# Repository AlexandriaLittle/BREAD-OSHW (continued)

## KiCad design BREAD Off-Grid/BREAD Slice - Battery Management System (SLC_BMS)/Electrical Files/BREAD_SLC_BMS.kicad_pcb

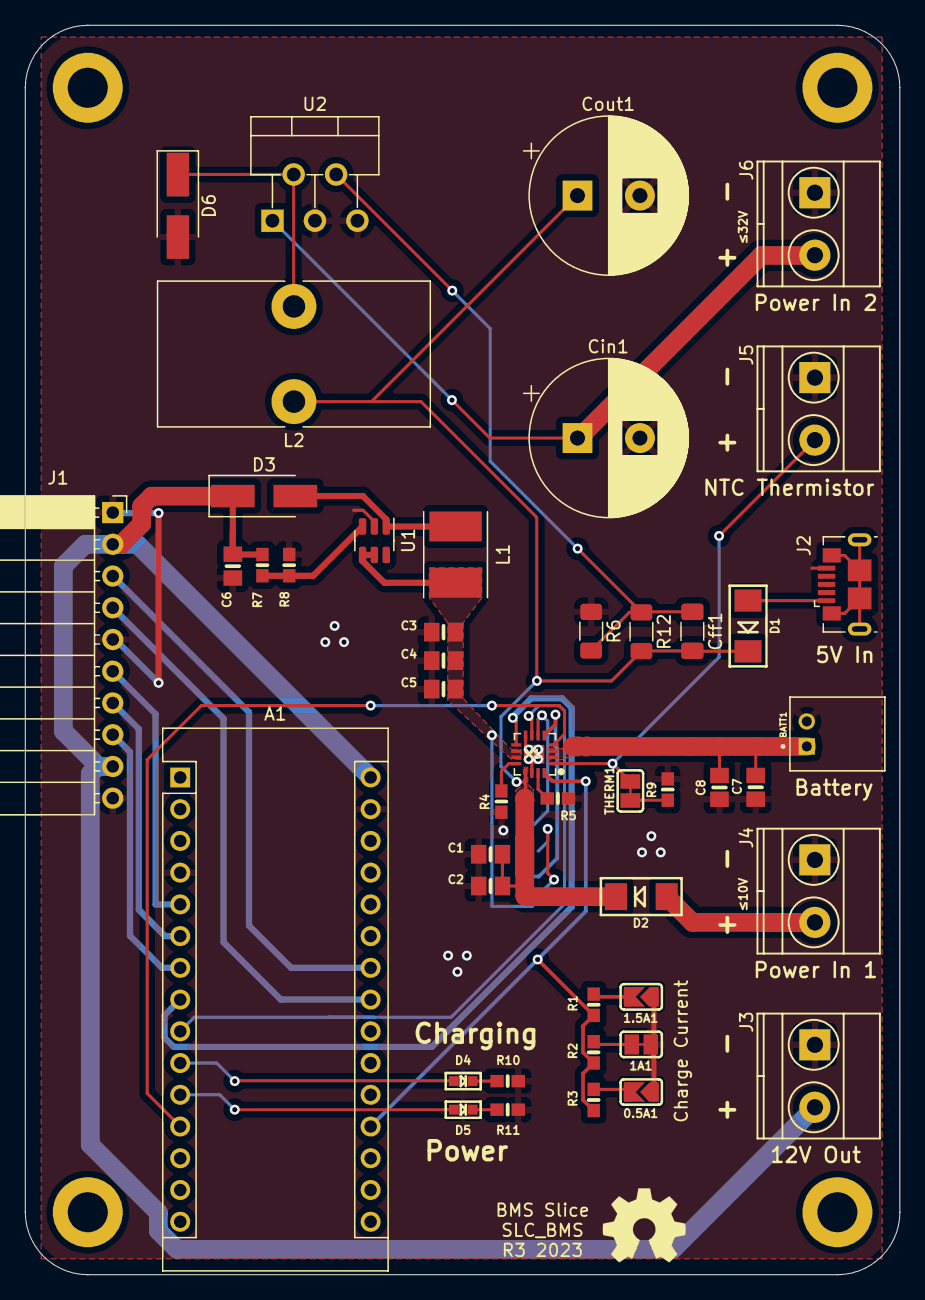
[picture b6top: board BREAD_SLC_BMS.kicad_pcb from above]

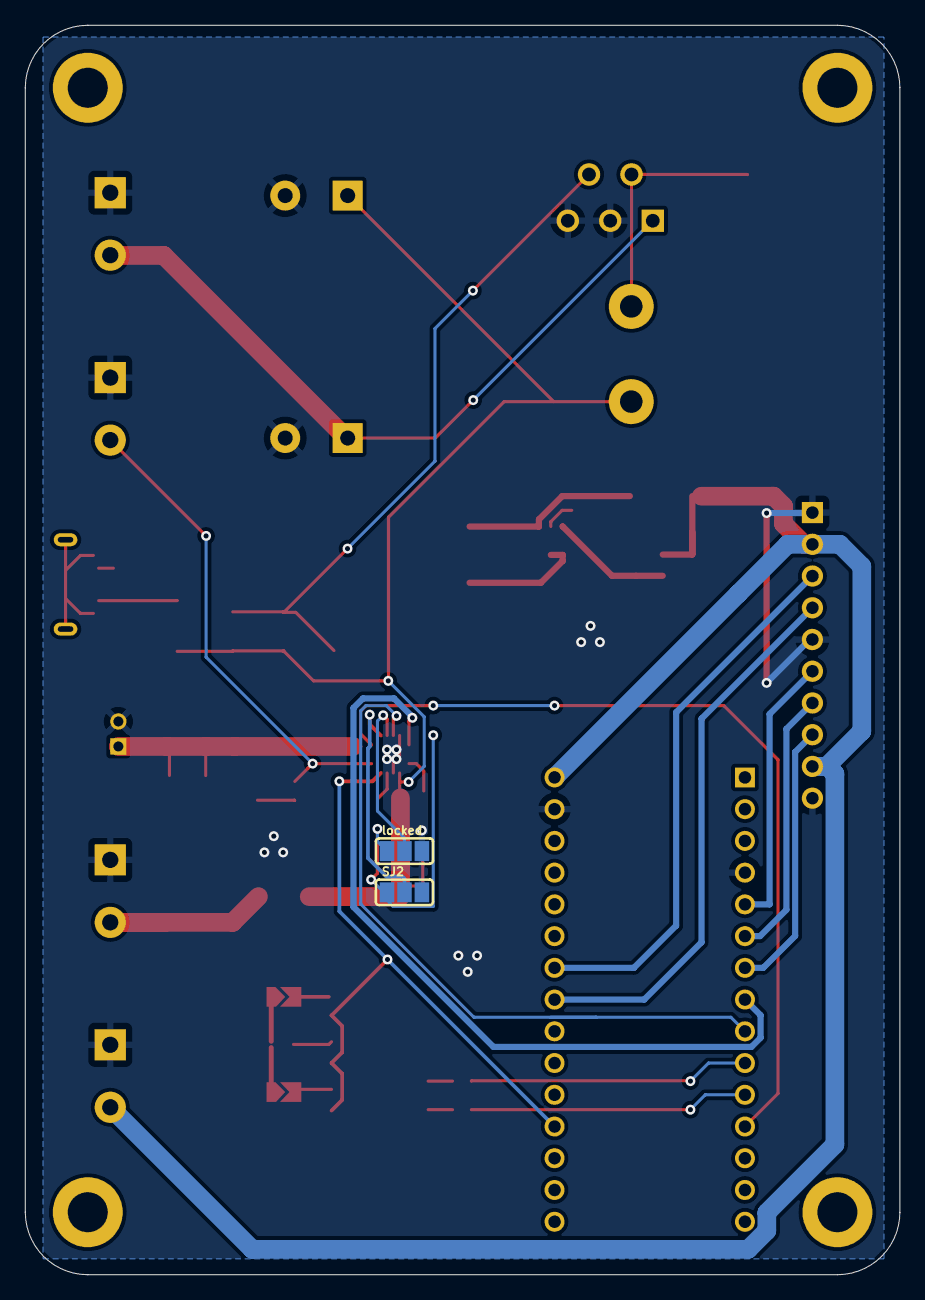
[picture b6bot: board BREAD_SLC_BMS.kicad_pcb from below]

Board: 2 copper layers, 70.0 x 100.0 mm, 53 parts (2 on the bottom side), 34 nets.

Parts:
0.5A1, 1.5A1: SOLDERJUMPER; SOLDERJUMPER_ARROW_NOPASTE
1A1: SOLDERJUMPERCLOSED; SOLDERJUMPER_CLOSEDWIRE
A1: Arduino_Nano_v3.x; Arduino_Nano
BATT1: JST 2PH; JST_S2B-PH-K-S(LF)(SN)
C1, C2, C7, C8: 10uF; 0805-NO
C3, C6: 22uF; 0805-NO
C4, C5: C; 0805-NO
Cff1: 3.3nF; C_1206_3216Metric_Pad1.33x1.80mm_HandSolder
Cin1: 680uF; CP_Radial_D12.5mm_P5.00mm
Cout1: 470uF; CP_Radial_D12.5mm_P5.00mm
D1, D2: SK34A; SMADIODE
D3, D6: D_Schottky; D_SMA_Handsoldering
D4: RED; CHIPLED_0603
D5: GREEN; CHIPLED_0603
H1, H2, H3, H4: MountingHole; MountingHole_3.2mm_M3_DIN965_Pad
J1: Conn_01x10_Female; PinSocket_1x10_P2.54mm_Horizontal
J2: USB_B_Micro; USB_Micro-B_GCT_USB3076-30-A
J3, J4, J5, J6: Screw_Terminal_01x02; TerminalBlock_Pheonix_MKDS1.5-2pol
L1: 22uH; L_Taiyo-Yuden_NR-50xx_HandSoldering
L2: 53uH; L_Toroid_Vertical_L21.6mm_W11.4mm_P7.62mm_Pulse_KM-3
Logo1: Logo_Open_Hardware_Small; OSHW-Symbol_6.7x6mm_SilkScreen
R1: 590; 0603-NO
R2, R4: 1K; 0603-NO
R3: 2K; 0603-NO
R5, R9, R10, R11: 10K; 0603-NO
R6: 1k; R_1206_3216Metric_Pad1.30x1.75mm_HandSolder
R7: 39k; 0603-NO
R8: 2.2k; 0603-NO
R12: 4.7k; R_1206_3216Metric_Pad1.30x1.75mm_HandSolder
SJ2: SOLDERJUMPER_2WAY; SOLDERJUMPER_2WAY_OPEN_NOPASTE
THERM1: SOLDERJUMPERCLOSED; SOLDERJUMPER_CLOSEDWIRE
U1: MT3608; SOT-23-6
U2: LM2596S-ADJ; TO-220-5_P3.4x3.7mm_StaggerOdd_Lead3.8mm_Vertical
X1: BQ24074; QFN16_3MM
locked: SOLDERJUMPER_2WAY; SOLDERJUMPER_2WAY_OPEN_NOPASTE

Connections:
/CHGI: A1.10 (D7), D4.A
/CHG_EN: A1.12 (D9), X1.4 (~CE)
/EN1: X1.6 (EN1), locked.2
/EN2: SJ2.2, X1.5 (EN2)
/E_STOP: A1.5 (D2), J1.6
/I2C_CLK: A1.24 (A5), J1.3
/I2C_DAT: A1.23 (A4), J1.4
/ILIM: R4.1, X1.12 (ILIM)
/INT: A1.6 (D3), J1.7
/ISET: A1.19 (A0), R1.1, R2.1, R3.1, X1.16 (ISET)
/ITERM: R5.1, X1.15 (ITERM)
/OUT: C3.1, C4.1, C5.1, L1.1, SJ2.1, U1.4 (EN), U1.5 (IN), X1.10 (OUT), X1.11 (OUT), locked.1
/PGOODI: A1.11 (D8), D5.A
/PWR: A1.30 (VIN), C6.1, D3.1 (K), J1.2, J1.9, J3.2, R7.1
/SYNC: A1.7 (D4), J1.8
/THERM: J5.2, THERM1.2, X1.1 (TS)
/Vmotor: Cin1.1, J6.2, U2.1 (VIN)
/~CHG: A1.8 (D5), X1.9 (~CHG)
/~PGOOD: A1.9 (D6), X1.7 (~PGOOD)
GND: 0.5A1.1, 1.5A1.1, 1A1.1, A1.4 (GND), A1.29 (GND), BATT1.2 (1), C1.2, C2.2, C3.2, C4.2, C5.2, C6.2, C7.2, C8.2, Cin1.2, Cout1.2, D6.2 (A), J1.1, J1.5, J1.10, J2.5 (GND), J3.1, J4.1, J5.1, J6.1, R4.2, R5.2, R6.1, R8.2, R9.2, R10.2, R11.2, SJ2.3, U1.2 (GND), U2.3 (GND), U2.5 (~ON/OFF), X1.8 (VSS), X1.14 (TMR), X1.THERMAL (VSS), locked.3
unnamed: 0.5A1.2, R3.2
unnamed: 1.5A1.2, R1.2
unnamed: 1A1.2, R2.2
unnamed: Cff1.1, R6.2, R12.1, U2.4 (FB)
unnamed: D1.A, J2.1 (VBUS)
unnamed: D2.A, J4.2
unnamed: D3.2 (A), L1.2, U1.1 (SW)
unnamed: D4.C, R10.1
unnamed: D5.C, R11.1
unnamed: D6.1 (K), L2.1, U2.2 (OUT)
unnamed: R7.2, R8.1, U1.3 (FB)
unnamed: R9.1, THERM1.1
VBUS: C1.1, C2.1, Cff1.2, Cout1.1, D1.C, D2.C, L2.2, R12.2, X1.13 (IN)
VLIPO: BATT1.1 (2), C7.1, C8.1, X1.2 (BAT), X1.3 (BAT)

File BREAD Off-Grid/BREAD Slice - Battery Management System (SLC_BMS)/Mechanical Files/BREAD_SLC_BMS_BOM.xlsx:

KiCad Reference | Part Number | Description | Value | Quantity | Unit Cost | Total Cost | Link
A1 | A000005 | Arduino Nano |  | 1 | 23.67 | 23.67 | https://store.arduino.cc/products/arduino-nano
 | PEC15SACN | Male headers | 0.1” pitch, 15-pin | 2 | 1.41 | 2.82 | https://www.digikey.com/en/products/detail/sullins-connector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
 | PPTC151LFBN-RC | Female headers | 0.1” pitch, 15-pin | 2 | 0.98 | 1.96 | https://www.digikey.com/en/products/detail/sullins-connector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
BATT1 | S2B-PH-K-S(LF)(SN) | Battery connector | 2 mm pitch, 2-position, right angle | 1 | 0.17 | 0.17 | https://www.digikey.com/en/products/detail/jst-sales-america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
C1, C2, C7, C8 | CL21A106KOQNNNE | Non-polarized capacitors | 10 μF, 0805 | 4 | 0.1 | 0.4 | https://www.digikey.com/en/products/detail/samsung-electro-m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
C3, C6 | CL21A226MOQNNNE | Non-polarized capacitors | 22 μF, 0805 | 2 | 0.27 | 0.54 | https://www.digikey.com/en/products/detail/samsung-electro-m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
Cff1 | C1206C332J5GAC7800 | Non-polarized capacitor | 3.3 nF, 1206 | 1 | 0.3 | 0.3 | https://www.digikey.com/en/products/detail/kemet/C1206C332J5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
Cin1 | EEU-FC1J681L | Polarized capacitor | 680 μF | 1 | 1.94 | 1.94 | https://www.digikey.com/en/products/detail/panasonic-electro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
Cout1 | EEU-FR1H471B | Polarized capacitor | 470 μF | 1 | 1.31 | 1.31 | https://www.digikey.com/en/products/detail/panasonic-electro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
D1, D2 | SK34A | Schottky diodes | SK34A | 2 | 0.49 | 0.98 | https://www.digikey.com/en/products/detail/smc-diode-solutio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
D3 | SS34-HF | Schottky diode | SS34 | 1 | 0.45 | 0.45 | https://www.digikey.com/en/products/detail/comchip-technolog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
D4 | B1911USD-20D000114U1930 | LED | Red, 0603 | 1 | 0.1 | 0.1 | https://www.digikey.com/en/products/detail/harvatek-corporat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
D5 | B1911NG--20D000214U1930 | LED | Green, 0603 | 1 | 0.1 | 0.1 | https://www.digikey.com/en/products/detail/harvatek-corporat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
D6 | CDBA540-HF | Schottky diode | CDBA540-HF | 1 | 0.44 | 0.44 | https://www.digikey.com/en/products/detail/comchip-technolog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
J1 | PPTC101LGBN-RC | Female header | 0.1” pitch, 10-pin, right angle | 1 | 0.76 | 0.76 | https://www.digikey.com/en/products/detail/sullins-connector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
J2 | USB3076-30-A | Micro USB connector | USB3076 | 1 | 0.7 | 0.7 | https://www.digikey.com/en/products/detail/gct/USB3076-30-A/9859635
J3 - J6 | 1935776 | Terminal blocks | 5mm pitch, 2-position, right angle | 4 | 0.59 | 2.36 | https://www.digikey.com/en/products/detail/phoenix-contact/1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
L1 | NRS5020T220MMGJ | Inductor | 22 μH | 1 | 0.3 | 0.3 | https://www.digikey.com/en/products/detail/taiyo-yuden/NRS50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
L2 | PE-54039NL | Inductor | 53 μH | 1 | 4.42 | 4.42 | https://www.digikey.com/en/products/detail/pulse-electronics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
R1 | RMCF0603FT590R | Resistor | 590Ω, 0603 | 1 | 0.1 | 0.1 | https://www.digikey.com/en/products/detail/stackpole-electro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
R2, R4 | RNCP0603FTD1K00 | Resistors | 1k Ω, 0603 | 2 | 0.1 | 0.2 | https://www.digikey.com/en/products/detail/stackpole-electro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
R3 | RMCF0603FT2K00 | Resistor | 2k Ω, 0603 | 1 | 0.1 | 0.1 | https://www.digikey.com/en/products/detail/stackpole-electro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
R5, R9 - R11 | RNCP0603FTD10K0 | Resistors | 10k Ω, 0603 | 4 | 0.1 | 0.4 | https://www.digikey.com/en/products/detail/stackpole-electro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
R6 | RMCF1206FT1K00 | Resistor | 1k Ω, 1206 | 1 | 0.1 | 0.1 | https://www.digikey.com/en/products/detail/stackpole-electro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
R7 | RMCF0603FT39K0 | Resistor | 39k Ω, 0603 | 1 | 0.1 | 0.1 | https://www.digikey.com/en/products/detail/stackpole-electro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
R8 | RMCF0603FT2K20 | Resistor | 2.2k Ω, 0603 | 1 | 0.1 | 0.1 | https://www.digikey.com/en/products/detail/stackpole-electro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
R12 | RMCF1206FT4K70 | Resistor | 4.7k Ω, 1206 | 1 | 0.1 | 0.1 | https://www.digikey.com/en/products/detail/stackpole-electro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
U1 | MT3608 | Boost converter | MT3608 | 1 | 0.09 | 0.43 | https://www.lcsc.com/product-detail/DC-DC-Converters_XI-AN-A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
U2 | LM2596TVADJG | Voltage regulator | LM2596 | 1 | 2.79 | 2.79 | https://www.digikey.com/en/products/detail/onsemi/LM2596TVAD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
X1 | BQ24074RGTR | Charging chip | BQ24074 | 1 | 3.45 | 3.45 | https://www.digikey.com/en/products/detail/texas-instruments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

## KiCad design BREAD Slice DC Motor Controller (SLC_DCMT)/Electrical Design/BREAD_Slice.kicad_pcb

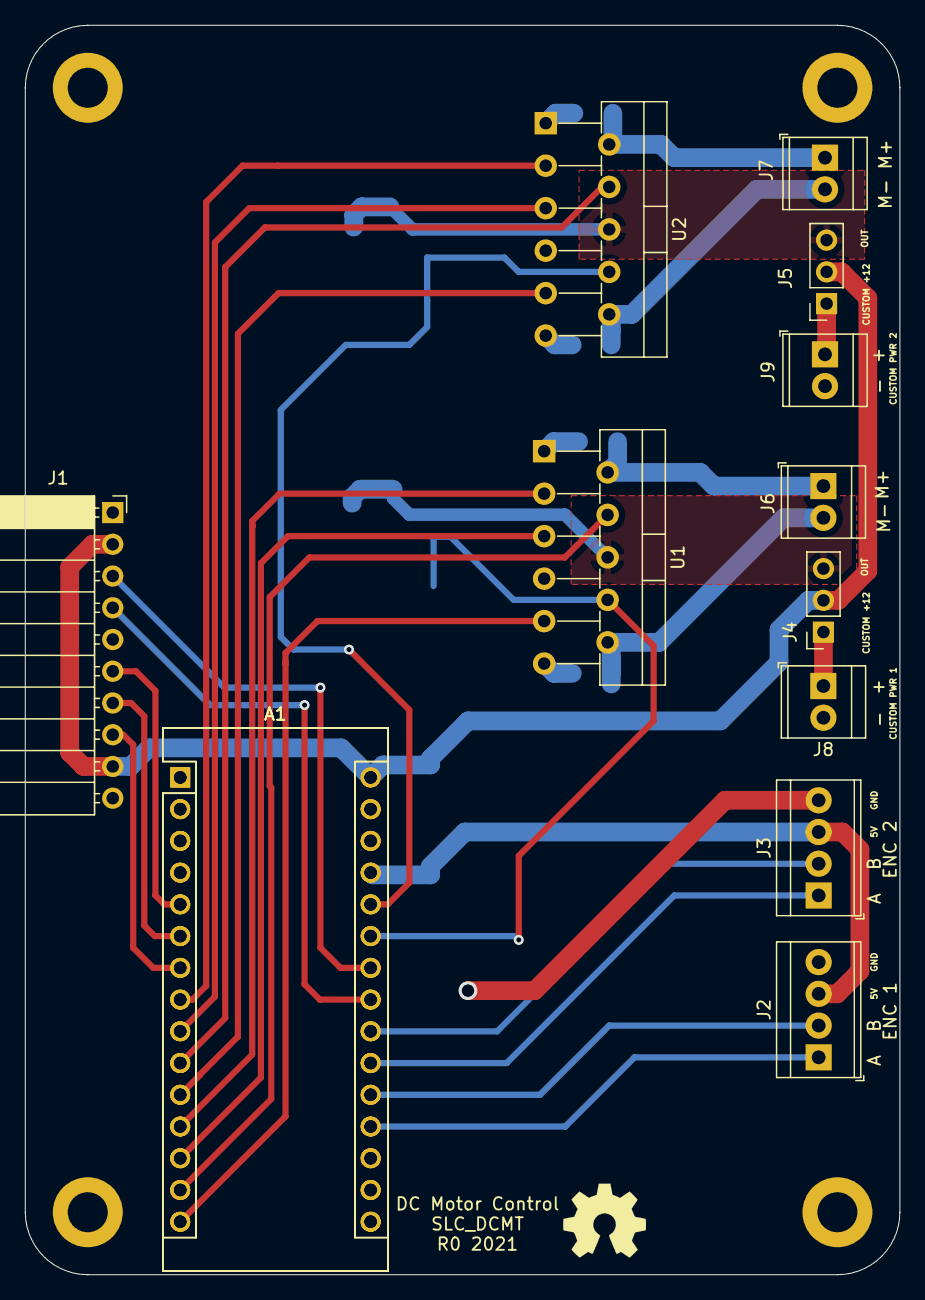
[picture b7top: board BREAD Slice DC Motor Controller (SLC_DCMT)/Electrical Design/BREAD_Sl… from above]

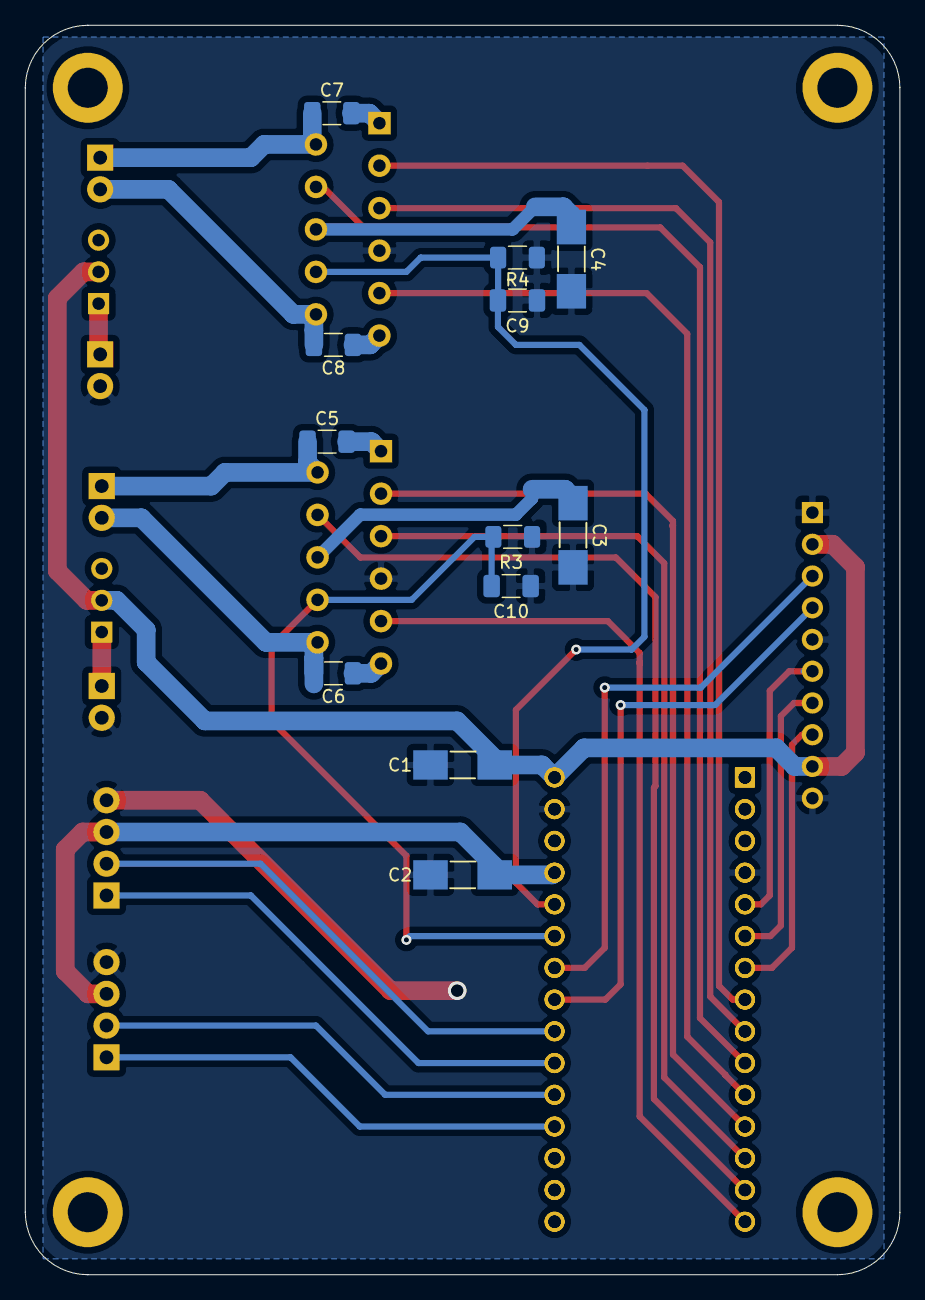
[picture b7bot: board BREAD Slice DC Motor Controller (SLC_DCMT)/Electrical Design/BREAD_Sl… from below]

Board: 2 copper layers, 70.0 x 100.0 mm, 30 parts (12 on the bottom side), 41 nets.

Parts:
A1, A1#2: Arduino_Nano_v3.x; Arduino_Nano
C1, C2, C3, C4: 10uF_t; C_2312
C5, C6, C7, C8, C9, C10: 10 nF; C_1206_3216Metric_Pad1.33x1.80mm_HandSolder
H1, H2, H3, H4: MountingHole; MountingHole_3.2mm_M3_DIN965_Pad
J1: Conn_01x10_Female; PinSocket_1x10_P2.54mm_Horizontal
J2, J3: Screw_Terminal_01x04; TerminalBlock_TE_282834-4_1x04_P2.54mm_Horizontal
J4, J5: Conn_01x03_Male; PinSocket_1x03_P2.54mm_Vertical
J6, J7, J8, J9: Screw_Terminal_01x02; TerminalBlock_TE_282834-2_1x02_P2.54mm_Horizontal
Logo1: Logo_Open_Hardware_Small; OSHW-Symbol_6.7x6mm_SilkScreen
R3, R4: 2.2 k; R_1206_3216Metric_Pad1.30x1.75mm_HandSolder
U1, U2: LMD18200; TO-220-11_P3.4x5.08mm_StaggerOdd_Lead4.85mm_Vertical

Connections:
+5V: A1.27, A1#2.27, C2.1, J2.3, J3.3
+12V: A1.30, A1#2.30, C1.1, J1.2, J1.9, J4.2, J5.2
/A1: A1.19, A1#2.19, J2.1
/A2: A1.21, A1#2.21, J3.1
/B1: A1.20, A1#2.20, J2.2
/B2: A1.22, A1#2.22, J3.2
/BR1: A1.14, A1#2.14, U1.4
/BR2: A1.10, A1#2.10, U2.4
/CSEN1: A1.25, A1#2.25, C10.1, R3.1, U1.8
/CSEN2: A1.26, A1#2.26, C9.1, R4.1, U2.8
/CUST1: J4.1, J8.1
/CUST2: J5.1, J9.1
/DIR1: A1.12, A1#2.12, U1.3
/DIR2: A1.8, A1#2.8, U2.3
/E_STOP: A1.5, A1#2.5, J1.6
/I2C_CLK: A1.24, A1#2.24, J1.3
/I2C_DAT: A1.23, A1#2.23, J1.4
/INT: A1.6, A1#2.6, J1.7
/MC1: A1.13, A1#2.13, U1.5
/MC2: A1.9, A1#2.9, U2.5
/SYNC: A1.7, A1#2.7, J1.8
/THRM1: A1.15, A1#2.15, U1.9
/THRM2: A1.11, A1#2.11, U2.9
GND: A1.4, A1.29, A1#2.4, A1#2.29, C1.2, C2.2, C3.2, C4.2, C9.2, C10.2, J1.1, J1.5, J1.10, J2.4, J3.4, J8.2, J9.2, R3.2, R4.2, U1.7, U2.7
unnamed: A1.1, A1#2.1
unnamed: A1.2, A1#2.2
unnamed: A1.3, A1#2.3
unnamed: A1.16, A1#2.16
unnamed: A1.17, A1#2.17
unnamed: A1.18, A1#2.18
unnamed: A1.28, A1#2.28
unnamed: C3.1, J4.3, U1.6
unnamed: C4.1, J5.3, U2.6
unnamed: C5.1, J6.1, U1.2
unnamed: C5.2, U1.1
unnamed: C6.1, U1.11
unnamed: C6.2, J6.2, U1.10
unnamed: C7.1, J7.1, U2.2
unnamed: C7.2, U2.1
unnamed: C8.1, U2.11
unnamed: C8.2, J7.2, U2.10

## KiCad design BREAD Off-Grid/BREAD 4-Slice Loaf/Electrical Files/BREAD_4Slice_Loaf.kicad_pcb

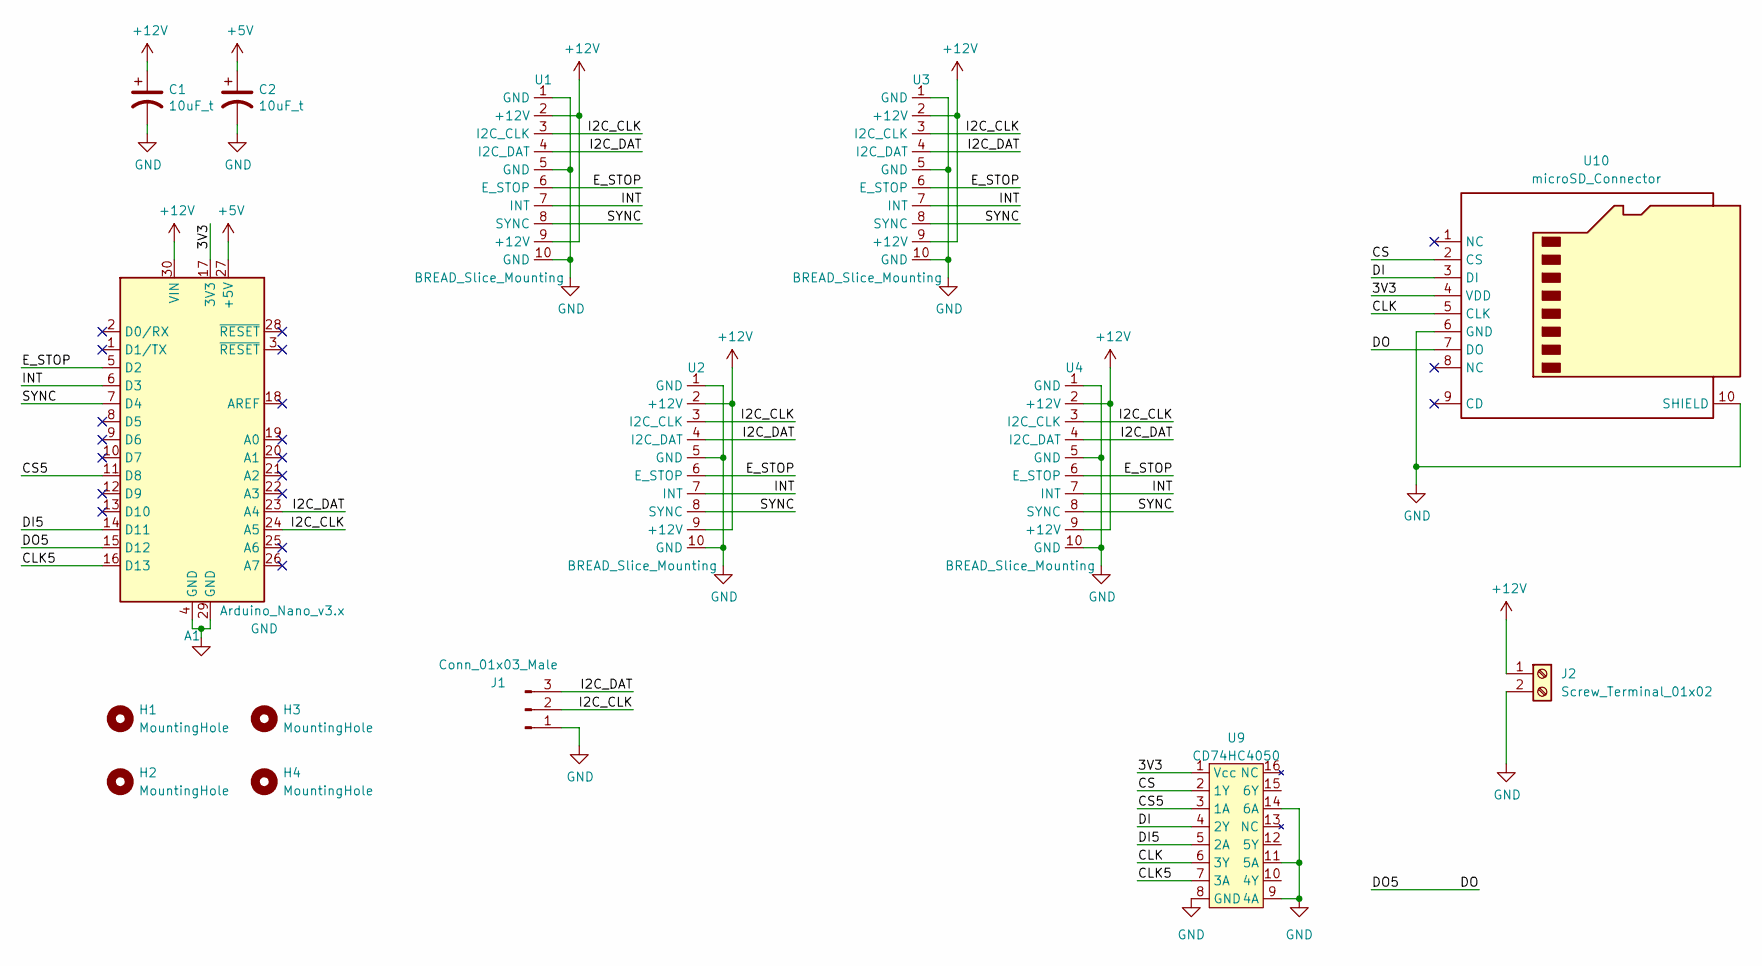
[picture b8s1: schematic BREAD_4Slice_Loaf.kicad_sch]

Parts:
A1: Arduino_Nano_v3.x; Arduino_Nano
C1, C2: 10uF_t; C_1206_3216Metric_Pad1.33x1.80mm_HandSolder; Part # T491C106K025AT
H1, H2, H3, H4: MountingHole; MountingHole_3.2mm_M3_DIN965_Pad
J1: Conn_01x03_Male; PinHeader_1x03_P2.54mm_Vertical
J2: Screw_Terminal_01x02; TerminalBlock_Phoenix_MKDS-1,5-2_1x02_P5.00mm_Horizontal
U1, U2, U3, U4: BREAD_Slice_Mounting
U9: CD74HC4050; DIP-16_W7.62mm_Socket_LongPads
U10: microSD_Connector; micro_SD_LOAF

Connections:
+5V: A1.27 (+5V), C2.1
+12V: A1.30 (VIN), C1.1, J2.1, U1.2 (+12V), U1.9 (+12V), U2.2 (+12V), U2.9 (+12V), U3.2 (+12V), U3.9 (+12V), U4.2 (+12V), U4.9 (+12V)
/3V3: A1.17 (3V3), U9.1 (Vcc), U10.4 (VDD)
/CLK: U9.6 (3Y), U10.5 (CLK)
/CLK5: A1.16 (D13), U9.7 (3A)
/CS: U9.2 (1Y), U10.2 (CS)
/CS5: A1.11 (D8), U9.3 (1A)
/DI: U9.4 (2Y), U10.3 (DI)
/DI5: A1.14 (D11), U9.5 (2A)
/DO: A1.15 (D12), U10.7 (DO)
/E_STOP: A1.5 (D2), U1.6 (E_STOP), U2.6 (E_STOP), U3.6 (E_STOP), U4.6 (E_STOP)
/I2C_CLK: A1.24 (A5), J1.2, U1.3 (I2C_CLK), U2.3 (I2C_CLK), U3.3 (I2C_CLK), U4.3 (I2C_CLK)
/I2C_DAT: A1.23 (A4), J1.3, U1.4 (I2C_DAT), U2.4 (I2C_DAT), U3.4 (I2C_DAT), U4.4 (I2C_DAT)
/INT: A1.6 (D3), U1.7 (INT), U2.7 (INT), U3.7 (INT), U4.7 (INT)
/SYNC: A1.7 (D4), U1.8 (SYNC), U2.8 (SYNC), U3.8 (SYNC), U4.8 (SYNC)
GND: A1.4 (GND), A1.29 (GND), C1.2, C2.2, J1.1, J2.2, U1.1 (GND), U1.5 (GND), U1.10 (GND), U2.1 (GND), U2.5 (GND), U2.10 (GND), U3.1 (GND), U3.5 (GND), U3.10 (GND), U4.1 (GND), U4.5 (GND), U4.10 (GND), U9.8 (GND), U9.9 (4A), U9.11 (5A), U9.14 (6A), U10.6 (GND), U10.10 (SHIELD)

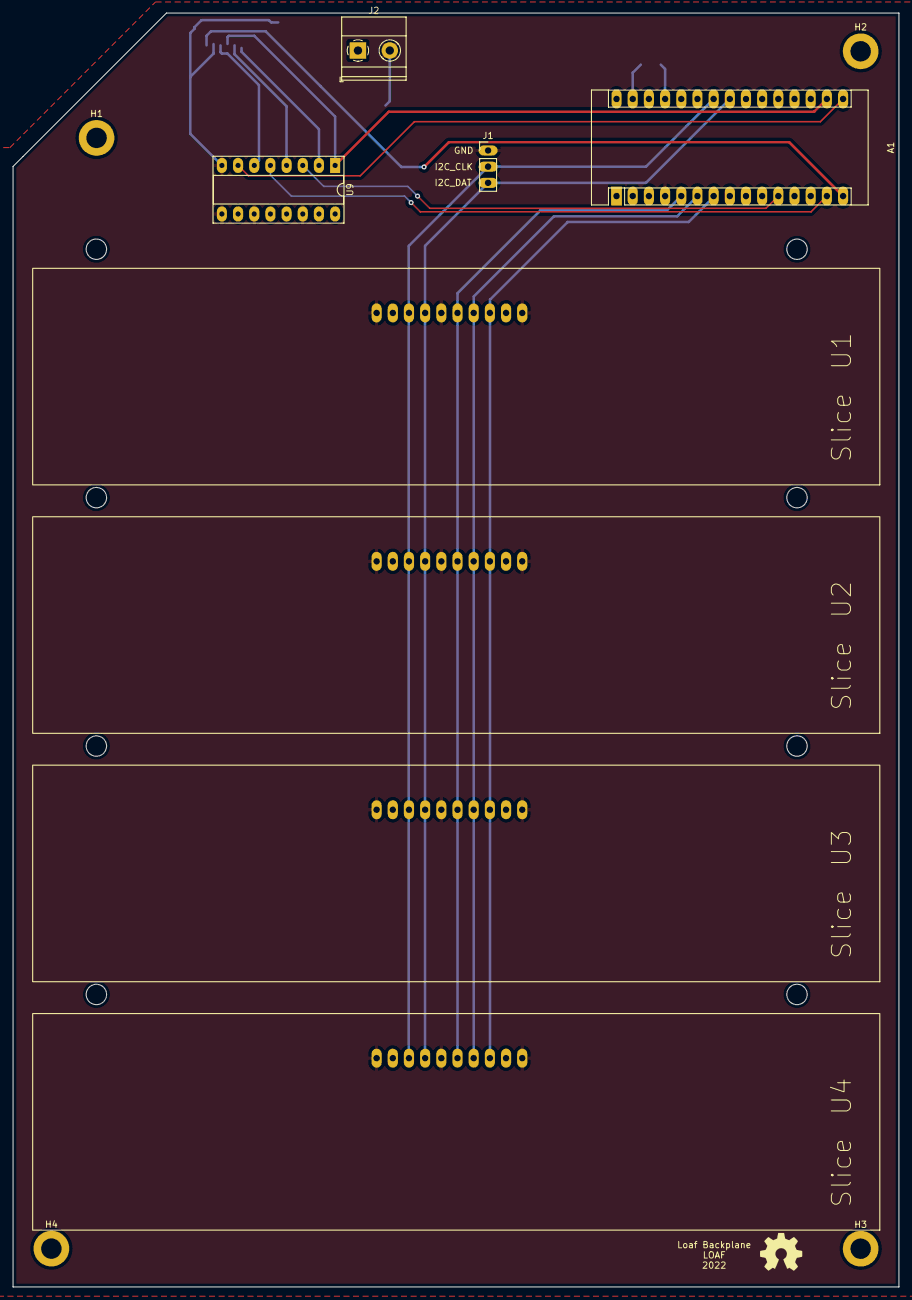
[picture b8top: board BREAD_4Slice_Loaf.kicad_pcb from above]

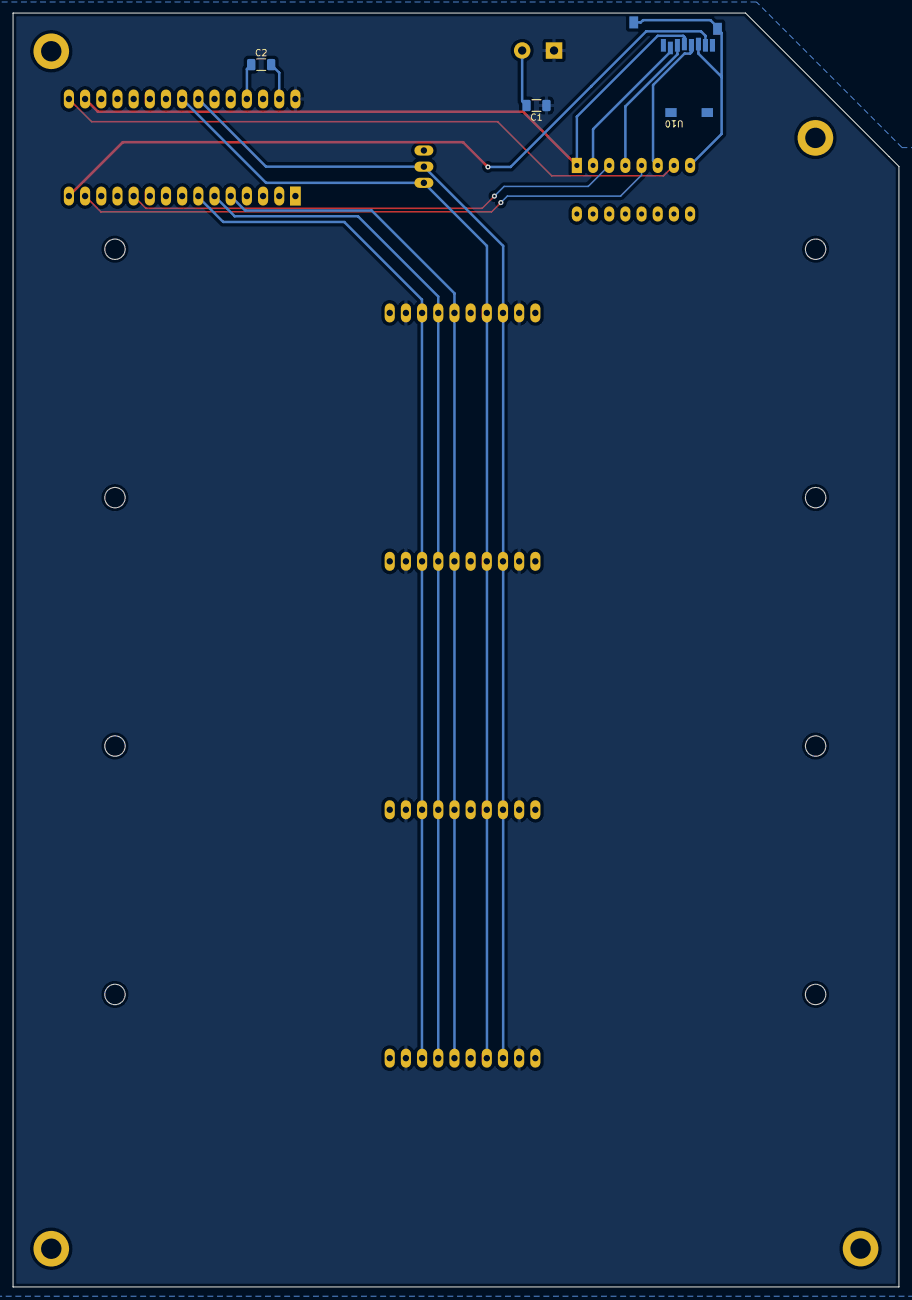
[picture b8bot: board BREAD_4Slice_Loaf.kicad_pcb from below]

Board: 2 copper layers, 139.1 x 200.0 mm, 16 parts (3 on the bottom side), 16 nets.

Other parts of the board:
Logo1: Logo_Open_Hardware_Small; OSHW-Symbol_6.7x6mm_SilkScreen

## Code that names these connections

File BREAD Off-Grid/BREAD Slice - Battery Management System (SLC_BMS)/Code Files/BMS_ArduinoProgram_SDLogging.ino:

#include <Wire.h>

int CHG_EN = 9; // active low
int CHGIN_ = 5; // active low
int PGOOD_ = 6; // active low
int CHGI = 7;   // CHG status LED
int PGOODI = 8; // Power good status LED
int ISET = A0;  // Used to monitor charging current
int BatV = A1;  // Future pin to read battery voltage.

int CHG_Status;
int POWER_Status;
int CHGV_Status;
int CHGI_Status;
int R_ISET = 1000;
int BatV_Status;

void setup() {
  //LOAF communication setup.
  Wire.begin(10);                 // join i2c bus with address #10
  Wire.onRequest(requestVoltage); // register event

  //Pin setup.
  pinMode(CHGIN_, INPUT_PULLUP);
  pinMode(PGOOD_, INPUT_PULLUP);
  pinMode(CHGI, OUTPUT);
  pinMode(PGOODI, OUTPUT);
  pinMode(CHG_EN, OUTPUT);

  //Sets charge enable pin to active.
  digitalWrite(CHG_EN,LOW);

  Serial.begin(9600);
}

void loop() {
  // update status LEDs.
  CHG_Status = !digitalRead(CHGIN_);
  POWER_Status = !digitalRead(PGOOD_);

  digitalWrite(CHGI, CHG_Status);
  digitalWrite(PGOODI, POWER_Status);

  // read and calculate charge current
  // This section uses the formula provided in the BQ24074 datasheet
  // and has not been proven to be functional

  //Rread Battery Voltage.
  BatV_Status = analogRead(BatV);
  // Read ISET
  CHGV_Status = analogRead(ISET);
  //CHGV_Status*1000;
  // Map read value to mV in order to avoid the need for decimals
  CHGV_Status = map(CHGV_Status, 0, 1023, 0, 5000);
  CHGI_Status = CHGV_Status * 400 / R_ISET;

  //Prints to help troubleshooting.
  Serial.print("CHG I: ");
  Serial.println(CHGI_Status);
  Serial.print("CHG V: ");
  Serial.println(CHGV_Status);
  Serial.print("Battery VOltage: ");
  Serial.println(BatV_Status);

  delay(200); // no need to update stuff more than 5x per second
}

// request code for SD & LOAF communication.
void requestVoltage(){
  char string[16];
  sprintf(string, "%d", CHGV_Status);
  Serial.println(string);
  Wire.write(string);
}

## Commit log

2026-01-14 Commit initial collection
2026-01-14 Add additional SLICE and LOAF
2026-01-14 Add links to sources in documentation
2026-01-14 Add links to README
2026-01-14 Fix typos
2026-01-14 Remove broken link
2026-04-06 Add Pressure Sensor Slice
2026-04-06 Fix README Typo
2026-04-17 Add prototyping slices as submodules
